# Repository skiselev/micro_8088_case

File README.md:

# Micro 8088 Case
Case for [Micro 8088](https://github.com/skiselev/micro_8088) and [ISA 8-Bit Backplane](https://github.com/skiselev/isa8_backplane) Based Computer

## Introduction
This case is intended to be used with [Micro 8088](https://github.com/skiselev/micro_8088)
and [ISA 8-Bit Backplane](https://github.com/skiselev/isa8_backplane) based computer.

The front panel features the standard [Intel* 9-pin front panel pinout](https://www.intel.com/content/www/us/en/support/articles/000007309/intel-nuc.html), and can work with other systems as well.

## Hardware Documentation

### 3D Printed Parts

Parts can be printed using PETG or other fillament. The parts are designed to be printed without supports, with the exception of the case back, which needs supports for the DC power connector area.

Part            | File                                                                                               | Notes
--------------- | -------------------------------------------------------------------------------------------------- | ------------------------------------------------------------------
Case Front      | [case_front.stl](https://github.com/skiselev/micro_8088_case/blob/master/printed/case_front.stl)   | For the system name in colored letters, print sytem_name.stl first
Case Back       | [case_back.stl](https://github.com/skiselev/micro_8088_case/blob/master/printed/case_back.stl)     |
Case Bottom     | [case_bottom.stl](https://github.com/skiselev/micro_8088_case/blob/master/printed/case_bottom.stl) | Use supports on the build plate only option when printing
Case Top        | [case_top.stl](https://github.com/skiselev/micro_8088_case/blob/master/printed/case_top.stl)       | It is possible to use a 192.8 mm * 192.8 mm piece of transparent 1/8" / 3 mm acrylic plastic instead
Case Left       | [case_left.stl](https://github.com/skiselev/micro_8088_case/blob/master/printed/case_left.stl)     |
Case Right      | [case_right.stl](https://github.com/skiselev/micro_8088_case/blob/master/printed/case_right.stl)   |
ISA Slots Cover | [slots_cover.stl](https://github.com/skiselev/micro_8088_case/blob/master/printed/slots_cover.stl) | Snaps into the Case Back
Speaker Bracket | [speaker_bracket.stl](https://github.com/skiselev/micro_8088_case/blob/master/printed/speaker_bracket.stl) |
System Name     | [system_name.stl](https://github.com/skiselev/micro_8088_case/blob/master/printed/system_name.stl) | System Name "Micro 8088". Print and remove the rectangle on the perimeter. Next print case_front.stl
Keycaps         | [keycap_6mm_round.stl](https://github.com/skiselev/micro_8088_case/blob/master/printed/keycap_6mm_round.stl) | Print two using colorful plastic. It is recommended to print several keycaps at the time. [Omron B32-2000](https://www.mouser.com/ProductDetail/653-B32-2000) keycaps can be used instead

### Other Parts

Part                       | Quantity  | Notes
-------------------------- | --------- | -----
M3 x 8 mm flat head screws | 16        | Hold case sides together
M3 x 1.8 mm square nuts    | 16        | Hold case sides together
M3 x 8 mm pan head screws  | 6         | Floppy drive
M3 x 6 mm pan head screws  | 15        | Backplane - 6 screws, front panel - 2 screws, ISA cards - 7 screws

### Front Panel Schematic and PCB Layout

[Schematic - Version 1.0](KiCad/Micro_8088_Front_Panel-Schematic-1.0.pdf)

[PCB Layout - Version 1.0](KiCad/Micro_8088_Front_Panel-Board-1.0.pdf)

### Jumpers, Connectors, and Switches

#### J1 - Front Panel Connector
Pin | Description                  | Pin | Description
--- | ---------------------------- | --- | -------------------
1   | HDD Activity LED Anode (+)   | 2   | Power LED Anode (+)
3   |	HDD Activity LED Cathode (-) | 4   | Power LED Cathode (-)
5   |	Reset Switch (Ground)        | 6   | Power Switch (Output)
7   |	Reset Switch (Output)        | 8   | Power Switch (Ground)
9   |	5V (Unused)                  | 10  | Key (Pin removed)

#### SW1 - Power Switch
Press SW1 to turn on/off the system

#### SW2 - Reset Switch
Press SW2 to reset the system

### Front Panel Bill of Material

[Micro 8088 Front Panel project on Mouser.com](https://www.mouser.com/ProjectManager/ProjectDetail.aspx?AccessID=e9e37fe2f8) - View and order all components except of the PCB.
[Micro 8088 Front Panel project on OSH Park](https://oshpark.com/shared_projects/V4toeD34) - View and order the PCB.

Component type     | Reference | Description                       | Quantity | Possible sources and notes 
------------------ | --------- | --------------------------------- | -------- | --------------------------
PCB                |           | Micro 8080 Front Panel PCB V1.0   | 1        | OSH Park [Micro 8088 Front Panel V1.0](https://oshpark.com/shared_projects/V4toeD34)<br>Alternatively order from a PCB manufacturer of your choice using provided KiCad files
LED                | D1        | 3 mm, blue LED indicator          | 1        | Mouser [604-WP710A10QBC/D](https://www.mouser.com/ProductDetail/604-WP710A10QBC-D)<br>Alternatively use 3 mm green LED<br>Note: Intel* specifies a bi-color green/yellow LED
LED                | D2        | 3 mm, pink LED indicator          | 1        | Mouser [604-WP7104VRVCWA](https://www.mouser.com/ProductDetail/604-WP7104VRVCWA)<br>Alternatively use 3 mm yellow LED
Tactile Button     | SW1, SW2  | 6 mm tactile button, projected    | 2        | Mouser [653-B3F-1052](https://www.mouser.com/ProductDetail/653-B3F-1052), [653-B3F-1050](https://www.mouser.com/ProductDetail/653-B3F-1050)
Key Cap            | SW1, SW2  | Omron 6 mm round keycap, black    | 2        | Mouser [653-B32-2000](https://www.mouser.com/ProductDetail/653-B32-2000). Or use 3D printed keycaps
Pin Header         | J1        | 2x5 pin header, 2.54 mm pitch     | 1        | Mouser [855-M20-9980545](https://www.mouser.com/ProductDetail/855-M20-9980545)
Speaker            |           | 36 mm x 4.6 mm, 8 ohm, 1 W        | 1        | Mouser [665-AS03608MRLW100R](https://www.mouser.com/ProductDetail/665-AS03608MRLW100R)

### Front Panel Cables Bill of Material

Component type     | Reference | Description                           | Quantity      | Possible sources and notes 
------------------ | --------- | ------------------------------------- | ------------- | --------------------------
Connector          | J1        | 2x5 pin wire housing, 2.54 mm pitch   | 1             | Front panel connector. Mouser [855-M20-1070500](https://www.mouser.com/ProductDetail/855-M20-1070500)
Connector          |           | 4 pin wire housing, 2.54 mm pitch     | 2             | Speaker connector. Power switch and Power LED connector for the ISA 8-bit backplane. Mouser [855-M20-1060400](https://www.mouser.com/ProductDetail/855-M20-1060400)
Connector          |           | 2 pin wire housing, 2.54 mm pitch     | 2             | Reset switch connector. HDD LED connector. Mouser [855-M20-1060200](https://www.mouser.com/ProductDetail/855-M20-1060200)
Contact            |           | Female crimp contact                  | 20            | All connectors. Mouser [855-M20-1160042](https://www.mouser.com/ProductDetail/855-M20-1160042), [855-M20-1180042](https://www.mouser.com/ProductDetail/855-M20-1180042)
Wire               |           | 22 AWG - 26 AWG stranded wire, white  | 60 cm or 2'   | Negative wires for LEDs and switches
Wire               |           | 22 AWG - 26 AWG stranded wire, black  | 10 cm or 1/3' | Negative wire for the speaker
Wire               |           | 22 AWG - 26 AWG stranded wire, red    | 30 cm or 1'   | Positive wire for the speaker and the HDD LED
Wire               |           | 22 AWG - 26 AWG stranded wire, green  | 10 cm or 1/3' | Positive wire for the Power LED
Wire               |           | 22 AWG - 26 AWG stranded wire, blue   | 30 cm or 1'   | Positive wire for the Reset switch
Wire               |           | 22 AWG - 26 AWG stranded wire, yellow | 10 cm or 1/3' | Positive wire for the Power switch

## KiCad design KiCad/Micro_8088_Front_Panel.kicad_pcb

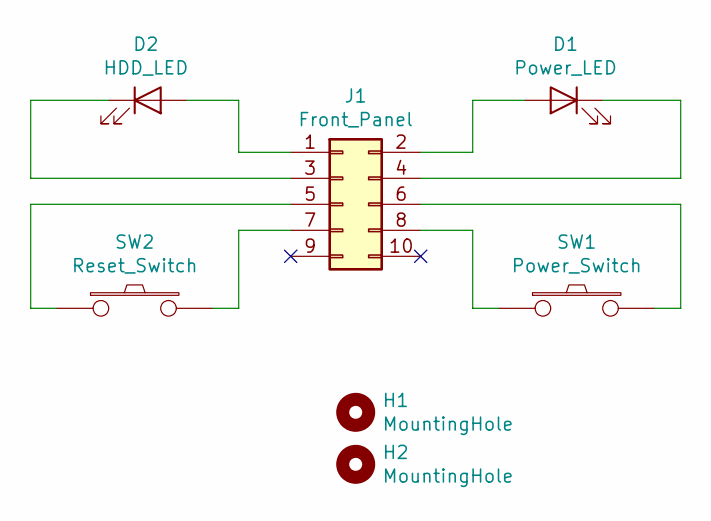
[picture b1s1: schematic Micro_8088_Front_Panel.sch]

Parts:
D1: Power_LED; LED_D3.0mm
D2: HDD_LED; LED_D3.0mm
H1, H2: MountingHole; MountingHole_3.2mm_M3_DIN965
J1: Front_Panel; PinHeader_2x05_P2.54mm_Vertical
SW1: Power_Switch; SW_PUSH_6mm_H7.3mm
SW2: Reset_Switch; SW_PUSH_6mm_H7.3mm

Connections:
unnamed: D1.1 (K), J1.4
unnamed: D1.2 (A), J1.2
unnamed: D2.1 (K), J1.3
unnamed: D2.2 (A), J1.1
unnamed: J1.5, SW2.1
unnamed: J1.6, SW1.2
unnamed: J1.7, SW2.2
unnamed: J1.8, SW1.1

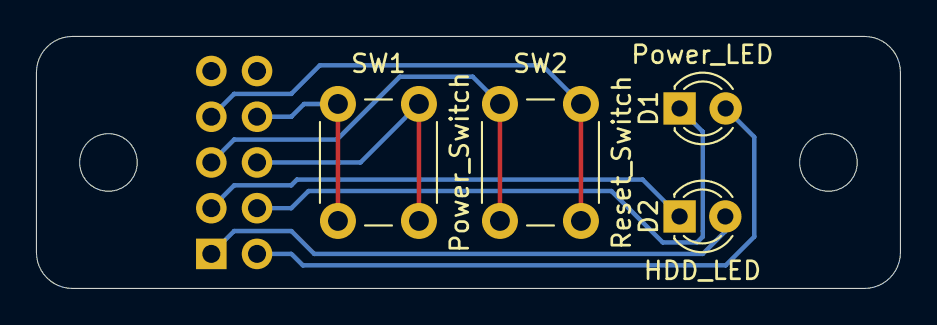
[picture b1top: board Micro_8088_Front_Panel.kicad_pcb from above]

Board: 2 copper layers, 48.0 x 14.0 mm, 7 parts (1 on the bottom side), 8 nets.

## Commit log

2019-04-09 .gitignore: Preserve netlist and cache
2019-04-09 Populate the repository with KiCad design files
2019-04-09 README: Create file
2019-04-09 README: Add links to schematic and PCB layout
2019-04-09 README: Add note about bi-color LEDs
2019-04-09 KiCad: Add PDF printouts
2023-10-10 Add OpenSCAD files for the case
2023-10-10 Cleanup - remove old modules
2023-10-10 Add conditions to print separate parts; Move slots_cover to X-Y plane
2023-10-10 Clean up OpenSCAD code, add STL files
2023-10-10 Clean up OpenSCAD code
2023-10-10 Upload a photo of the case
2023-10-10 Reduce image size
2023-10-10 Update README.md - Add case parts description
2023-11-03 Use 3.0 mm thickness for the case walls
2023-11-03 Replace case photo with a new one
2023-11-17 Fix front panel pinout link. Add BOM for the front panel cables
2025-02-08 README: Add speaker to the BOM

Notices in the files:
KiCad/Micro_8088_Front_Panel.kicad_pcb:
License:
GPLv3
Copyright (C) 2019
